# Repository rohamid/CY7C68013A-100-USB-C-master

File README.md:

# CY7C68013A 100 pins dev board
Here is yet another CY7C68013A 100 pins with USB C connection.

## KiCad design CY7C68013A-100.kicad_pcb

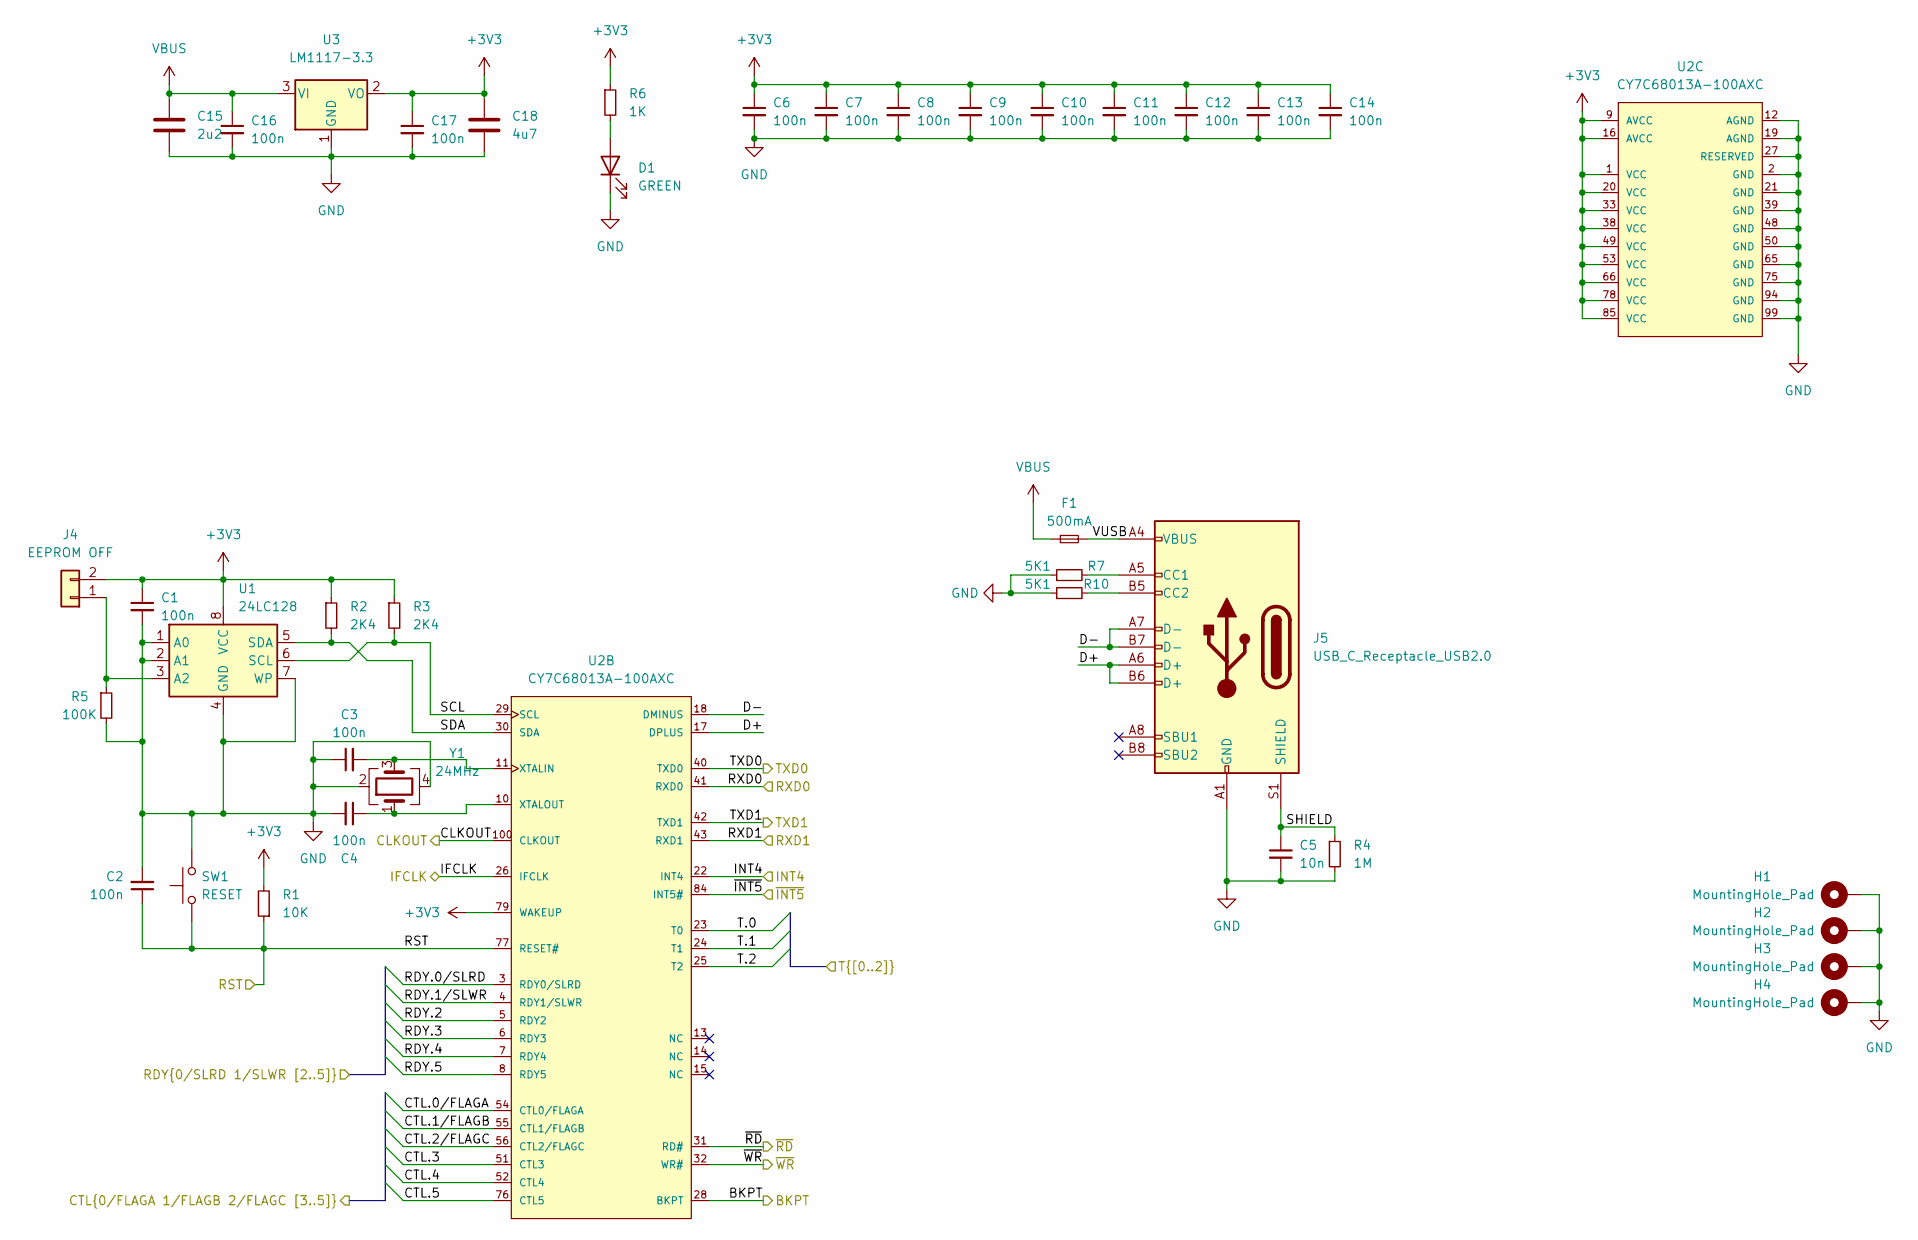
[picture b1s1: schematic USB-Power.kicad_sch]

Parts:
C1, C2, C3, C4, C6, C7, C8, C9, C10, C11, C12, C13, C14, C16, C17: 100n; C_0402_1005Metric; LCSC Part Number C307331
C5: 10n; C_1206_3216Metric; LCSC Part Number C35216
C15: 2u2; C_0805_2012Metric; LCSC Part Number C49217
C18: 4u7; C_0805_2012Metric; LCSC Part Number C1779
D1: GREEN; LED_0805_2012Metric; LCSC Part Number C34499
F1: 500mA; Fuse_0805_2012Metric; LCSC Part Number C269104
H1, H2, H3, H4: MountingHole_Pad; MountingHole_3.2mm_M3_Pad_Via
J4: EEPROM OFF; PinHeader_1x02_P2.54mm_Vertical
J5: USB_C_Receptacle_USB2.0; USB_C_Receptacle_G-Switch_GT-USB-7010ASV
R1: 10K; R_0402_1005Metric; LCSC Part Number C25744
R2, R3: 2K4; R_0402_1005Metric; LCSC Part Number C25862
R4: 1M; R_0805_2012Metric; LCSC Part Number C17514
R5: 100K; R_0402_1005Metric; LCSC Part Number C25741
R6: 1K; R_0402_1005Metric; LCSC Part Number C11702
R7, R10: 5K1; R_0402_1005Metric; LCSC Part Number C25744
SW1: RESET; SW_Push_1P1T_NO_CK_KMR2; LCSC Part Number C115360
U1: 24LC128; SOIC-8_3.9x4.9mm_P1.27mm; LCSC Part Number C99368
U2: CY7C68013A-100AXC; PQFP-100_14x20mm_P0.65mm; LCSC Part Number C9926
U3: LM1117-3.3; SOT-223-3_TabPin2; LCSC Part Number C6186
Y1: 24MHz; Crystal_SMD_3225-4Pin_3.2x2.5mm; LCSC Part Number C2650460

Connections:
+3V3: C1.1, C6.1, C7.1, C8.1, C9.1, C10.1, C11.1, C12.1, C13.1, C14.1, C17.1, C18.1, J4.2, R1.2, R2.1, R3.1, R6.1, U1.8 (VCC), U2.1 (VCC), U2.9 (AVCC), U2.16 (AVCC), U2.20 (VCC), U2.33 (VCC), U2.38 (VCC), U2.49 (VCC), U2.53 (VCC), U2.66 (VCC), U2.78 (VCC), U2.79 (WAKEUP), U2.85 (VCC), U3.2 (VO); also elsewhere on the board
/GPIO/BKPT: U2.28 (BKPT); also elsewhere on the board
/GPIO/CLKOUT: U2.100 (CLKOUT); also elsewhere on the board
/GPIO/CTL.0/FLAGA: U2.54 (CTL0/FLAGA); also elsewhere on the board
/GPIO/CTL.1/FLAGB: U2.55 (CTL1/FLAGB); also elsewhere on the board
/GPIO/CTL.2/FLAGC: U2.56 (CTL2/FLAGC); also elsewhere on the board
/GPIO/CTL.3: U2.51 (CTL3); also elsewhere on the board
/GPIO/CTL.4: U2.52 (CTL4); also elsewhere on the board
/GPIO/CTL.5: U2.76 (CTL5); also elsewhere on the board
/GPIO/IFCLK: U2.26 (IFCLK); also elsewhere on the board
/GPIO/INT4: U2.22 (INT4); also elsewhere on the board
/GPIO/RDY.0/SLRD: U2.3 (RDY0/SLRD); also elsewhere on the board
/GPIO/RDY.1/SLWR: U2.4 (RDY1/SLWR); also elsewhere on the board
/GPIO/RDY.2: U2.5 (RDY2); also elsewhere on the board
/GPIO/RDY.3: U2.6 (RDY3); also elsewhere on the board
/GPIO/RDY.4: U2.7 (RDY4); also elsewhere on the board
/GPIO/RDY.5: U2.8 (RDY5); also elsewhere on the board
/GPIO/T.0: U2.23 (T0); also elsewhere on the board
/GPIO/T.1: U2.24 (T1); also elsewhere on the board
/GPIO/T.2: U2.25 (T2); also elsewhere on the board
/GPIO/~INT5: U2.84 (INT5#); also elsewhere on the board
/GPIO/~RD: U2.31 (RD#); also elsewhere on the board
/GPIO/~WR: U2.32 (WR#); also elsewhere on the board
/USB-Power/D+: J5.A6 (D+), J5.B6 (D+), U2.17 (DPLUS)
/USB-Power/D-: J5.A7 (D-), J5.B7 (D-), U2.18 (DMINUS)
/USB-Power/RST: C2.1, R1.1, SW1.1, U2.77 (RESET#)
/USB-Power/RXD0: U2.41 (RXD0); also elsewhere on the board
/USB-Power/RXD1: U2.43 (RXD1); also elsewhere on the board
/USB-Power/SCL: R3.2, U1.6 (SCL), U2.29 (SCL)
/USB-Power/SDA: R2.2, U1.5 (SDA), U2.30 (SDA)
/USB-Power/SHIELD: C5.1, J5.S1 (SHIELD), R4.1
/USB-Power/TXD0: U2.40 (TXD0); also elsewhere on the board
/USB-Power/TXD1: U2.42 (TXD1); also elsewhere on the board
/USB-Power/VUSB: F1.2, J5.A4 (VBUS), J5.A9 (VBUS), J5.B4 (VBUS), J5.B9 (VBUS)
GND: C1.2, C2.2, C3.1, C4.2, C5.2, C6.2, C7.2, C8.2, C9.2, C10.2, C11.2, C12.2, C13.2, C14.2, C15.2, C16.2, C17.2, C18.2, D1.1 (K), H1.1, H2.1, H3.1, H4.1, J5.A1 (GND), J5.A12 (GND), J5.B1 (GND), J5.B12 (GND), R4.2, R5.2, R7.1, R10.1, SW1.2, U1.1 (A0), U1.2 (A1), U1.4 (GND), U1.7 (WP), U2.2 (GND), U2.12 (AGND), U2.19 (AGND), U2.21 (GND), U2.27 (RESERVED), U2.39 (GND), U2.48 (GND), U2.50 (GND), U2.65 (GND), U2.75 (GND), U2.94 (GND), U2.99 (GND), U3.1 (GND), Y1.2, Y1.4; also elsewhere on the board
unnamed: C3.2, U2.11 (XTALIN), Y1.3
unnamed: C4.1, U2.10 (XTALOUT), Y1.1
unnamed: D1.2 (A), R6.2
unnamed: J4.1, R5.1, U1.3 (A2)
unnamed: J5.A5 (CC1), R7.2
unnamed: J5.B5 (CC2), R10.2
VBUS: C15.1, C16.1, F1.1, U3.3 (VI); also elsewhere on the board

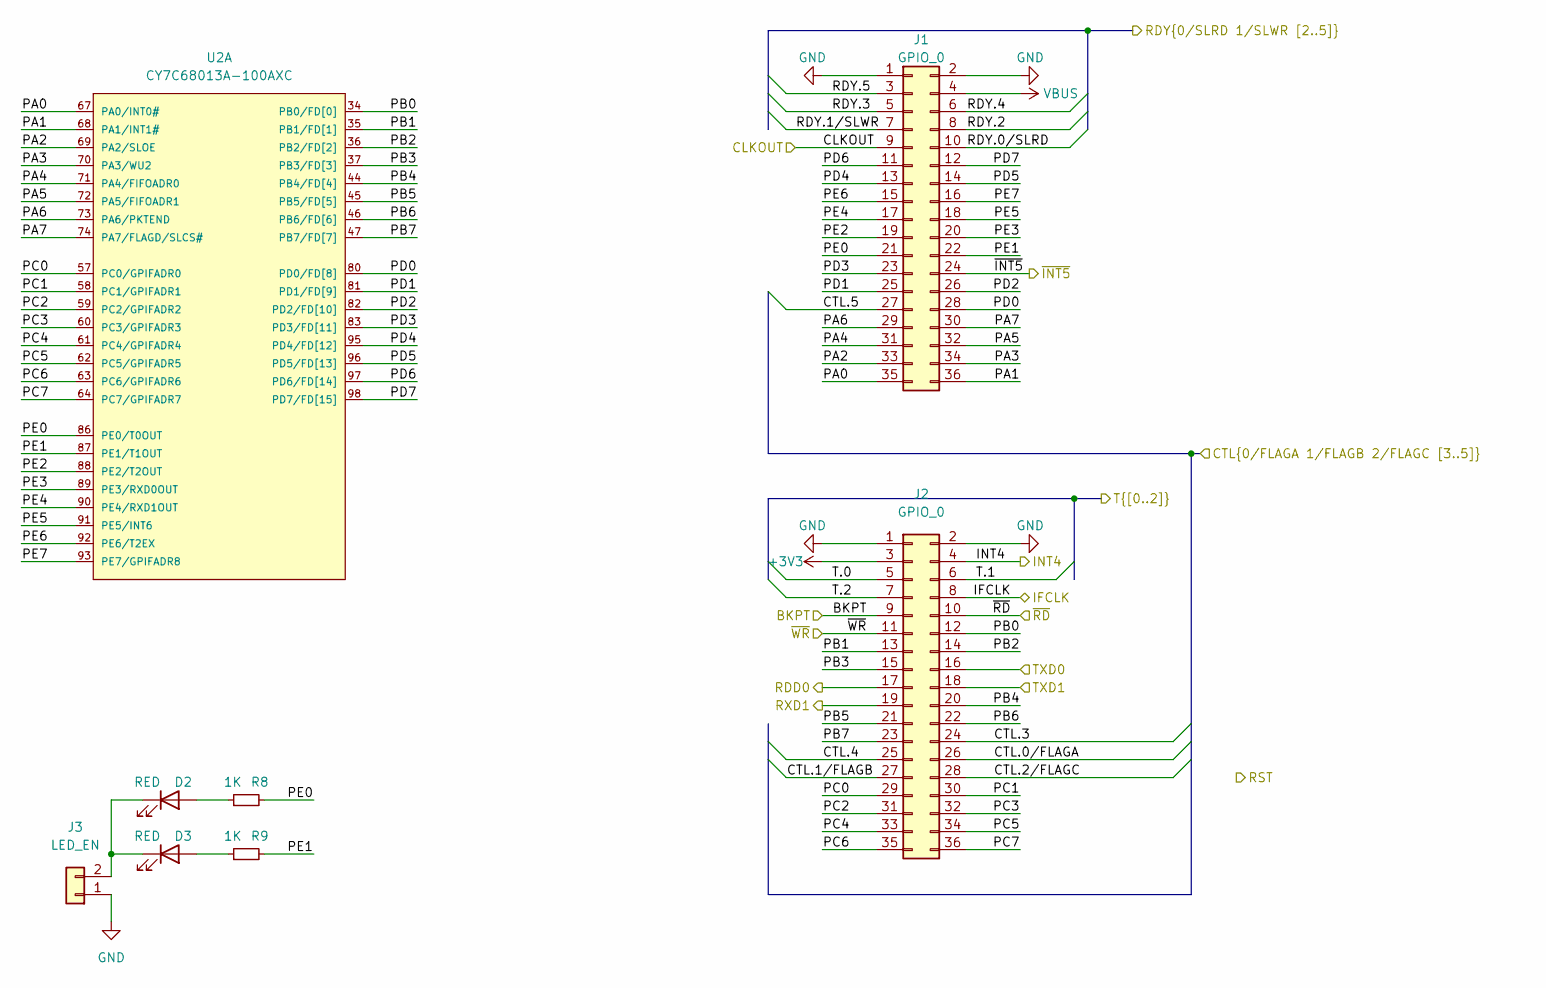
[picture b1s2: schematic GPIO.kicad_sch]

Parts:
D2, D3: RED; LED_0805_2012Metric; LCSC Part Number C84256
J1, J2: GPIO_0; PinHeader_2x18_P2.54mm_Vertical
J3: LED_EN; PinHeader_1x02_P2.54mm_Vertical
R8, R9: 1K; R_0402_1005Metric; LCSC Part Number C11702
U2: CY7C68013A-100AXC; PQFP-100_14x20mm_P0.65mm; LCSC Part Number C9926

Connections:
+3V3: J2.3; also elsewhere on the board
/GPIO/BKPT: J2.9; also elsewhere on the board
/GPIO/CLKOUT: J1.9; also elsewhere on the board
/GPIO/CTL.0/FLAGA: J2.26; also elsewhere on the board
/GPIO/CTL.1/FLAGB: J2.27; also elsewhere on the board
/GPIO/CTL.2/FLAGC: J2.28; also elsewhere on the board
/GPIO/CTL.3: J2.24; also elsewhere on the board
/GPIO/CTL.4: J2.25; also elsewhere on the board
/GPIO/CTL.5: J1.27; also elsewhere on the board
/GPIO/IFCLK: J2.8; also elsewhere on the board
/GPIO/INT4: J2.4; also elsewhere on the board
/GPIO/PA0: J1.35, U2.67 (PA0/INT0#)
/GPIO/PA1: J1.36, U2.68 (PA1/INT1#)
/GPIO/PA2: J1.33, U2.69 (PA2/SLOE)
/GPIO/PA3: J1.34, U2.70 (PA3/WU2)
/GPIO/PA4: J1.31, U2.71 (PA4/FIFOADR0)
/GPIO/PA5: J1.32, U2.72 (PA5/FIFOADR1)
/GPIO/PA6: J1.29, U2.73 (PA6/PKTEND)
/GPIO/PA7: J1.30, U2.74 (PA7/FLAGD/SLCS#)
/GPIO/PB0: J2.12, U2.34 (PB0/FD[0])
/GPIO/PB1: J2.13, U2.35 (PB1/FD[1])
/GPIO/PB2: J2.14, U2.36 (PB2/FD[2])
/GPIO/PB3: J2.15, U2.37 (PB3/FD[3])
/GPIO/PB4: J2.20, U2.44 (PB4/FD[4])
/GPIO/PB5: J2.21, U2.45 (PB5/FD[5])
/GPIO/PB6: J2.22, U2.46 (PB6/FD[6])
/GPIO/PB7: J2.23, U2.47 (PB7/FD[7])
/GPIO/PC0: J2.29, U2.57 (PC0/GPIFADR0)
/GPIO/PC1: J2.30, U2.58 (PC1/GPIFADR1)
/GPIO/PC2: J2.31, U2.59 (PC2/GPIFADR2)
/GPIO/PC3: J2.32, U2.60 (PC3/GPIFADR3)
/GPIO/PC4: J2.33, U2.61 (PC4/GPIFADR4)
/GPIO/PC5: J2.34, U2.62 (PC5/GPIFADR5)
/GPIO/PC6: J2.35, U2.63 (PC6/GPIFADR6)
/GPIO/PC7: J2.36, U2.64 (PC7/GPIFADR7)
/GPIO/PD0: J1.28, U2.80 (PD0/FD[8])
/GPIO/PD1: J1.25, U2.81 (PD1/FD[9])
/GPIO/PD2: J1.26, U2.82 (PD2/FD[10])
/GPIO/PD3: J1.23, U2.83 (PD3/FD[11])
/GPIO/PD4: J1.13, U2.95 (PD4/FD[12])
/GPIO/PD5: J1.14, U2.96 (PD5/FD[13])
/GPIO/PD6: J1.11, U2.97 (PD6/FD[14])
/GPIO/PD7: J1.12, U2.98 (PD7/FD[15])
/GPIO/PE0: J1.21, R8.2, U2.86 (PE0/T0OUT)
/GPIO/PE1: J1.22, R9.2, U2.87 (PE1/T1OUT)
/GPIO/PE2: J1.19, U2.88 (PE2/T2OUT)
/GPIO/PE3: J1.20, U2.89 (PE3/RXD0OUT)
/GPIO/PE4: J1.17, U2.90 (PE4/RXD1OUT)
/GPIO/PE5: J1.18, U2.91 (PE5/INT6)
/GPIO/PE6: J1.15, U2.92 (PE6/T2EX)
/GPIO/PE7: J1.16, U2.93 (PE7/GPIFADR8)
/GPIO/RDY.0/SLRD: J1.10; also elsewhere on the board
/GPIO/RDY.1/SLWR: J1.7; also elsewhere on the board
/GPIO/RDY.2: J1.8; also elsewhere on the board
/GPIO/RDY.3: J1.5; also elsewhere on the board
/GPIO/RDY.4: J1.6; also elsewhere on the board
/GPIO/RDY.5: J1.3; also elsewhere on the board
/GPIO/T.0: J2.5; also elsewhere on the board
/GPIO/T.1: J2.6; also elsewhere on the board
/GPIO/T.2: J2.7; also elsewhere on the board
/GPIO/~INT5: J1.24; also elsewhere on the board
/GPIO/~RD: J2.10; also elsewhere on the board
/GPIO/~WR: J2.11; also elsewhere on the board
/USB-Power/RXD0: J2.17; also elsewhere on the board
/USB-Power/RXD1: J2.19; also elsewhere on the board
/USB-Power/TXD0: J2.16; also elsewhere on the board
/USB-Power/TXD1: J2.18; also elsewhere on the board
GND: J1.1, J1.2, J2.1, J2.2, J3.1; also elsewhere on the board
unnamed: D2.1 (K), D3.1 (K), J3.2
unnamed: D2.2 (A), R8.1
unnamed: D3.2 (A), R9.1
VBUS: J1.4; also elsewhere on the board

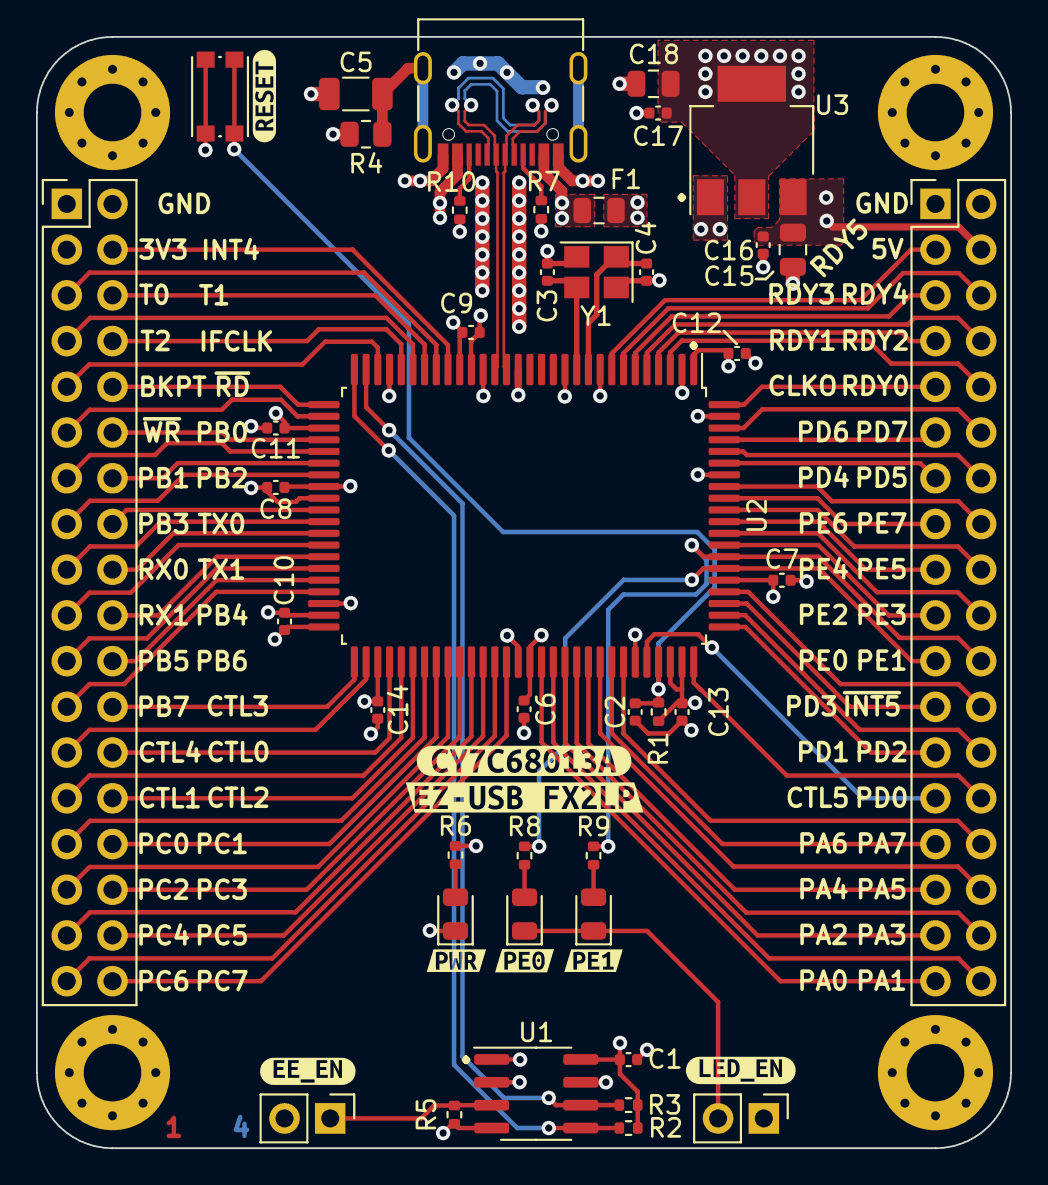
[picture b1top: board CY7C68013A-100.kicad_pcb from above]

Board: 4 copper layers, 54.1 x 61.7 mm, 54 parts (0 on the bottom side), 85 nets.

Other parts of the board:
kibuzzard-63EC9B5B: G***; kibuzzard-63EC9B5B
kibuzzard-63EC9B77: G***; kibuzzard-63EC9B77
kibuzzard-63EC60C6: G***; kibuzzard-63EC60C6
kibuzzard-63EC608B: G***; kibuzzard-63EC608B
kibuzzard-63EED3F1: G***; kibuzzard-63EED3F1
kibuzzard-63FDDF2A: G***; kibuzzard-63FDDF2A
kibuzzard-63FDDF21: G***; kibuzzard-63FDDF21
kibuzzard-63FDDF30: G***; kibuzzard-63FDDF30
